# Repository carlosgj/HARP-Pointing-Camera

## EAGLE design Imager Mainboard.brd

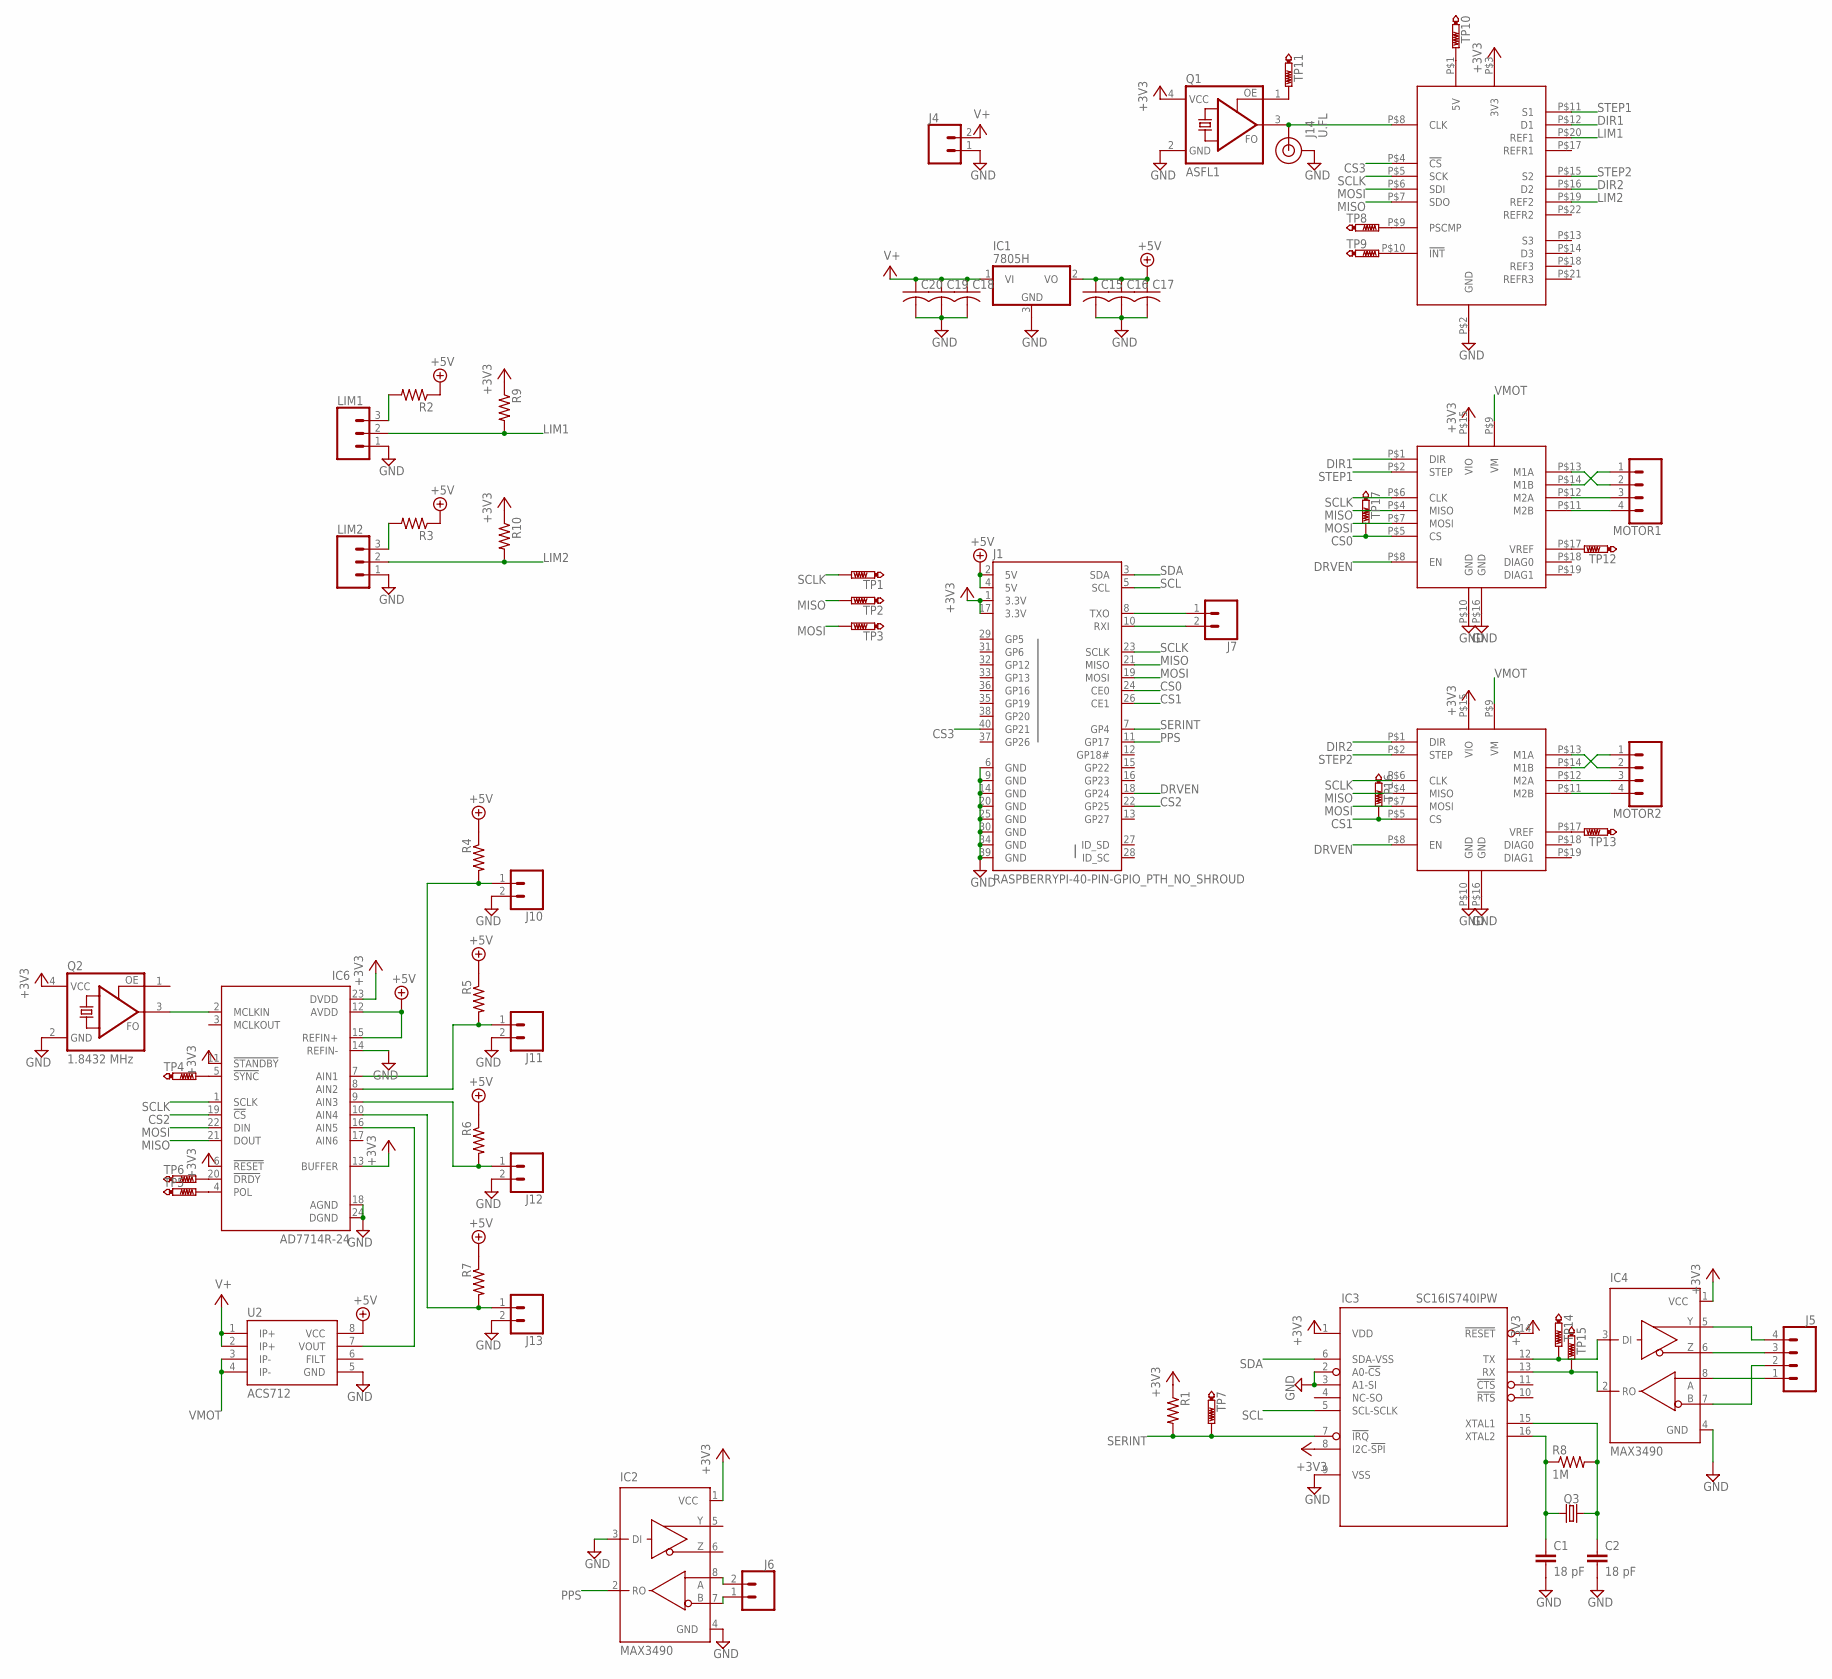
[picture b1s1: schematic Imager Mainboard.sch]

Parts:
C1, C2: 18 pF; C1206
C15, C16, C17, C18, C19, C20: C-USC1206; C1206
DRV1, DRV2: SILENTSTEPSTICK
IC1: 7805H; TO39
IC2, IC4: MAX3490; SO08
IC3: SC16IS740IPW; TSSOP16L
IC6: AD7714R-24; SO24R
J1: RASPBERRYPI-40-PIN-GPIO_PTH_NO_SHROUD; 2X20
J4, J6, J7, J10, J11, J12, J13: CONN_02; 1X02
J5: CONN_04; 1X04
J14: U.FL
LIM1, LIM2: CONN_03; 1X03
MOTOR1, MOTOR2: CONN_04; 1X04
Q1: ASFL1; ASF
Q2: 1.8432 MHz; ASF
Q3: CRYSTALSMD-5X3.2-4PAD; CRYSTAL-SMD-5X3.2-4PAD
R1, R2, R3, R4, R5, R6, R7, R9, R10: R-US_R1206; R1206
R8: 1M; R1206
TP1, TP2, TP3, TP8, TP9, TP10, TP11, TP12, TP13, TP14, TP15, TP16, TP17: PTR1PAD1-13; P1-13
TP4, TP5, TP6, TP7: PTR1B1,27; B1,27
U2: ACS712; SO08
U$1: TMC429-BOB

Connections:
+3V3: DRV1.P$15 (VIO), DRV2.P$15 (VIO), IC2.1 (VCC), IC3.1 (VDD), IC3.8 (I2C-!SPI), IC3.14 (!RESET), IC4.1 (VCC), IC6.6 (!RESET), IC6.11 (!STANDBY), IC6.13 (BUFFER), IC6.23 (DVDD), J1.1 (3.3V), J1.17 (3.3V), Q1.4 (VCC), Q2.4 (VCC), R1.1, R9.1, R10.1, U$1.P$3 (3V3)
+5V: C15.1, C16.1, C17.1, IC1.2 (VO), IC6.12 (AVDD), IC6.15 (REFIN+), J1.2 (5V), J1.4 (5V), R2.1, R3.1, R4.1, R5.1, R6.1, R7.1, U2.8 (VCC)
CS0: DRV1.P$5 (CS), J1.24 (CE0), TP17.TP
CS1: DRV2.P$5 (CS), J1.26 (CE1), TP16.TP
CS2: IC6.19 (!CS), J1.22 (GP25)
CS3: J1.40 (GP21), U$1.P$4 (!CS)
DIR1: DRV1.P$1 (DIR), U$1.P$12 (D1)
DIR2: DRV2.P$1 (DIR), U$1.P$16 (D2)
DRVEN: DRV1.P$8 (EN), DRV2.P$8 (EN), J1.18 (GP24)
GND: C1.2, C2.2, C15.2, C16.2, C17.2, C18.2, C19.2, C20.2, DRV1.P$10 (GND), DRV1.P$16 (GND), DRV2.P$10 (GND), DRV2.P$16 (GND), IC1.3 (GND), IC2.3 (DI), IC2.4 (GND), IC3.2 (A0-!CS), IC3.3 (A1-SI), IC3.9 (VSS), IC4.4 (GND), IC6.14 (REFIN-), IC6.18 (AGND), IC6.24 (DGND), J1.6 (GND), J1.9 (GND), J1.14 (GND), J1.20 (GND), J1.25 (GND), J1.30 (GND), J1.34 (GND), J1.39 (GND), J4.1, J10.2, J11.2, J12.2, J13.2, J14.1 (GND), J14.2 (GND), LIM1.1, LIM2.1, Q1.2 (GND), Q2.2 (GND), U2.5 (GND), U$1.P$2 (GND)
LIM1: LIM1.2, R9.2, U$1.P$20 (REF1)
LIM2: LIM2.2, R10.2, U$1.P$19 (REF2)
MISO: DRV1.P$4 (MISO), DRV2.P$4 (MISO), IC6.21 (DOUT), J1.21 (MISO), TP2.TP, U$1.P$7 (SDO)
MOSI: DRV1.P$7 (MOSI), DRV2.P$7 (MOSI), IC6.22 (DIN), J1.19 (MOSI), TP3.TP, U$1.P$6 (SDI)
unnamed: DRV2.P$14 (M1B), MOTOR2.1
unnamed: DRV2.P$13 (M1A), MOTOR2.2
unnamed: IC3.12 (TX), IC4.3 (DI), TP14.TP
unnamed: DRV2.P$12 (M2A), MOTOR2.3
unnamed: DRV2.P$11 (M2B), MOTOR2.4
unnamed: DRV1.P$14 (M1B), MOTOR1.1
unnamed: DRV1.P$13 (M1A), MOTOR1.2
unnamed: DRV1.P$12 (M2A), MOTOR1.3
unnamed: DRV1.P$11 (M2B), MOTOR1.4
unnamed: J1.8 (TXO), J7.1
unnamed: J1.10 (RXI), J7.2
unnamed: IC6.2 (MCLKIN), Q2.3 (FO)
unnamed: IC6.5 (!SYNC), TP4.TP
unnamed: LIM1.3, R2.2
unnamed: J14.FEED (SIGNAL), Q1.3 (FO), U$1.P$8 (CLK)
unnamed: LIM2.3, R3.2
unnamed: IC6.4 (POL), TP5.TP
unnamed: IC6.16 (AIN5), U2.7 (VOUT)
unnamed: IC6.20 (!DRDY), TP6.TP
unnamed: IC6.7 (AIN1), J10.1, R4.2
unnamed: TP8.TP, U$1.P$9 (PSCMP)
unnamed: IC6.8 (AIN2), J11.1, R5.2
unnamed: IC6.9 (AIN3), J12.1, R6.2
unnamed: IC6.10 (AIN4), J13.1, R7.2
unnamed: TP9.TP, U$1.P$10 (!INT)
unnamed: TP10.TP, U$1.P$1 (5V)
unnamed: Q1.1 (OE), TP11.TP
unnamed: DRV1.P$17 (VREF), TP12.TP
unnamed: DRV2.P$17 (VREF), TP13.TP
unnamed: C2.1, IC3.15 (XTAL1), Q3.3 (2), R8.2
unnamed: C1.1, IC3.16 (XTAL2), Q3.1, R8.1
unnamed: IC3.13 (RX), IC4.2 (RO), TP15.TP
unnamed: IC4.6 (Z), J5.3
unnamed: IC4.8 (A), J5.1
unnamed: IC4.7 (B), J5.2
unnamed: IC4.5 (Y), J5.4
unnamed: IC2.7 (B), J6.1
unnamed: IC2.8 (A), J6.2
PPS: IC2.2 (RO), J1.11 (GP17)
SCL: IC3.5 (SCL-SCLK), J1.5 (SCL)
SCLK: DRV1.P$6 (CLK), DRV2.P$6 (CLK), IC6.1 (SCLK), J1.23 (SCLK), TP1.TP, U$1.P$5 (SCK)
SDA: IC3.6 (SDA-VSS), J1.3 (SDA)
SERINT: IC3.7 (!IRQ), J1.7 (GP4), R1.2, TP7.TP
STEP1: DRV1.P$2 (STEP), U$1.P$11 (S1)
STEP2: DRV2.P$2 (STEP), U$1.P$15 (S2)
V+: C18.1, C19.1, C20.1, IC1.1 (VI), J4.2, U2.1 (IP+), U2.2 (IP+)
VMOT: DRV1.P$9 (VM), DRV2.P$9 (VM), U2.3 (IP-), U2.4 (IP-)

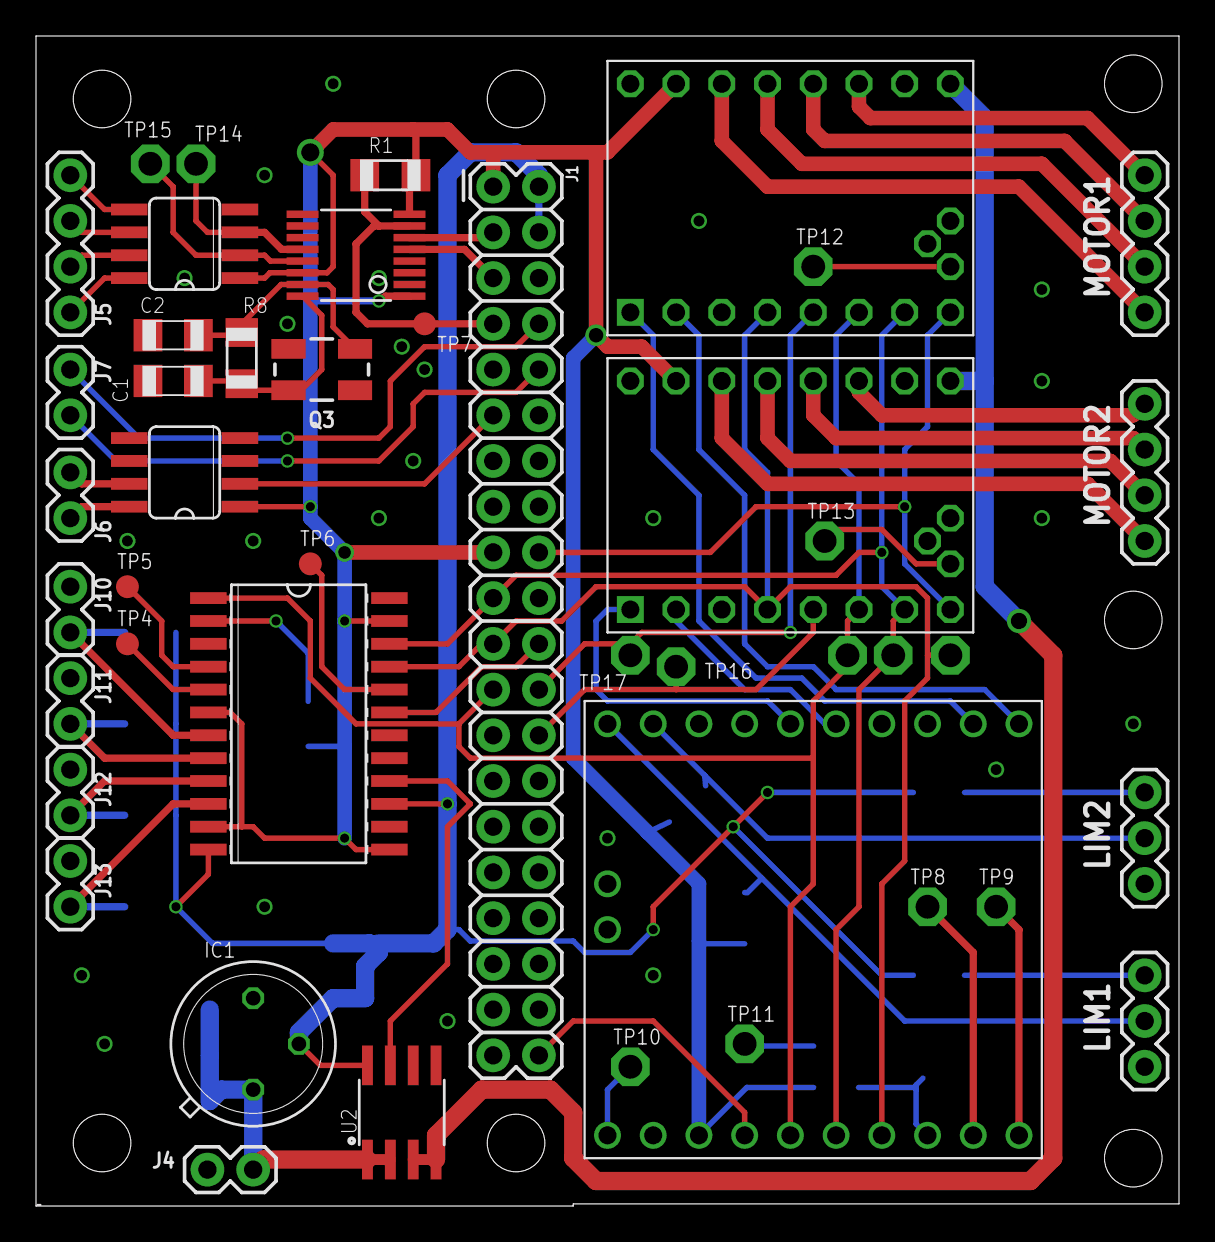
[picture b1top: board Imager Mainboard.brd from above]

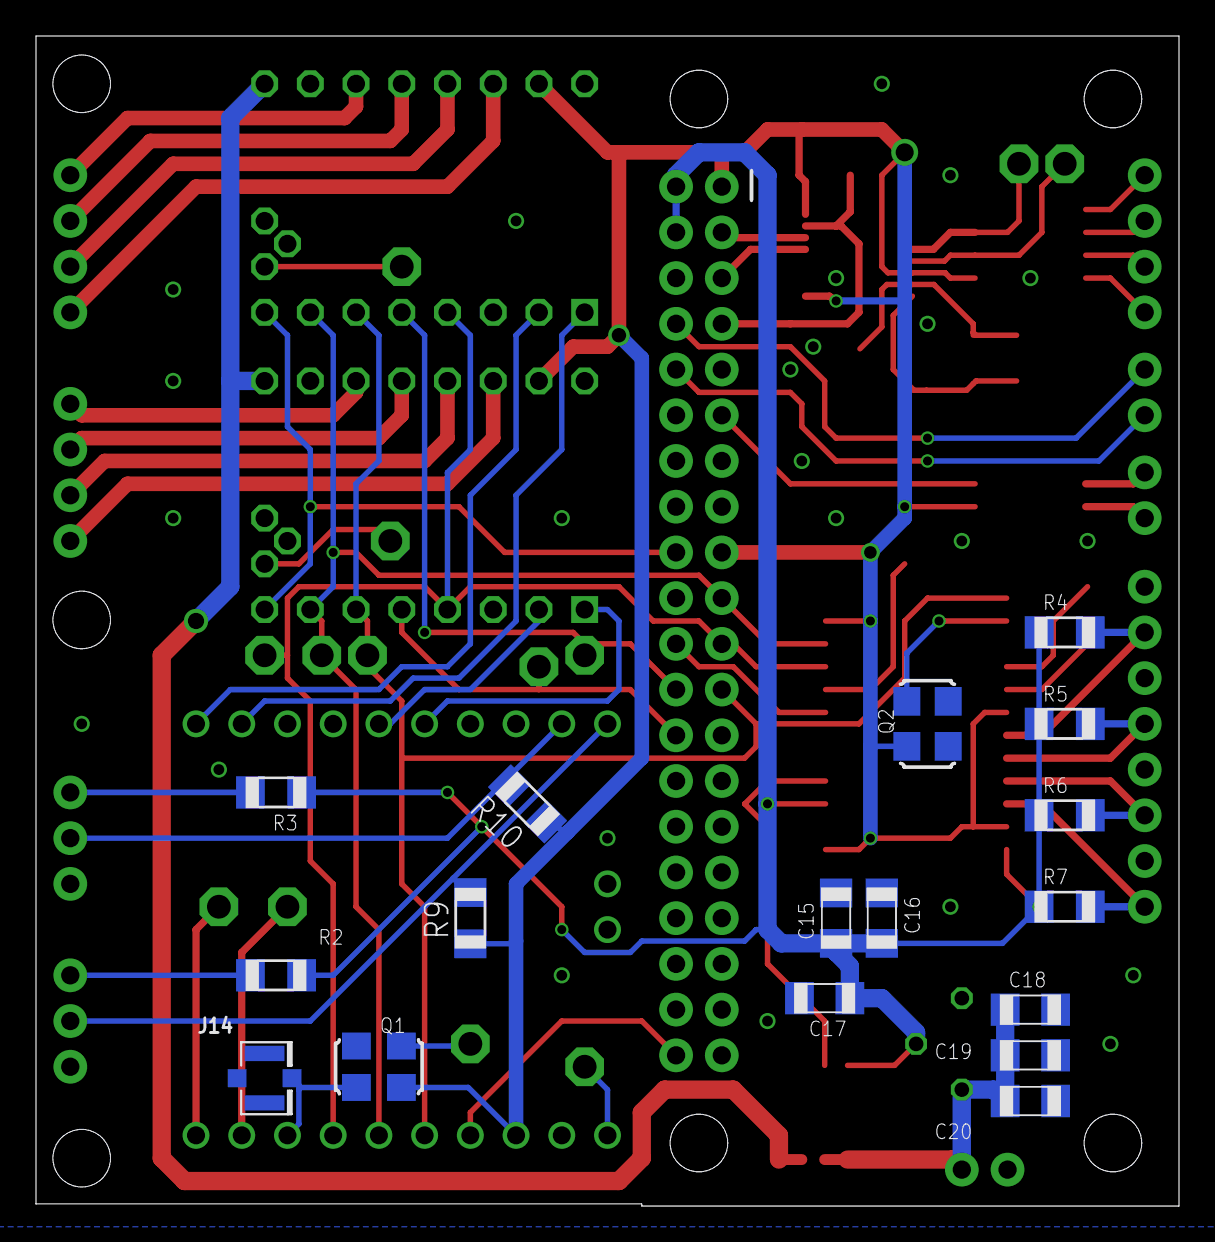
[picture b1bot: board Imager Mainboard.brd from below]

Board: 2 copper layers, 63.5 x 65.0 mm, 61 parts (17 on the bottom side), 61 nets.

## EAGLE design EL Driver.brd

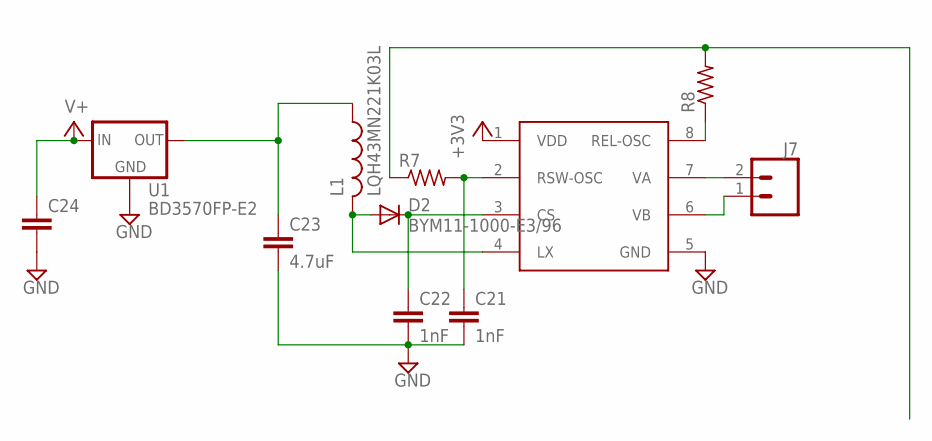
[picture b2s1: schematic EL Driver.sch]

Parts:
C21, C22: 1nF; C1206
C23: 4.7uF; C1206
C24: C-EUC1206; C1206
D2: BYM11-1000-E3/96; MELF-MLL41
J7: CONN_02; 1X02
L1: LQH43MN221K03L; L1812
R7, R8: R-US_R1206; R1206
U1: BD3570FP-E2; TO-252
U$3: HV830; SOIC8

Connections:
+3V3: U$3.1 (VDD)
GND: C21.2, C22.2, C23.2, C24.2, U1.3 (GND), U$3.5 (GND)
unnamed: J7.2, U$3.7 (VA)
unnamed: J7.1, U$3.6 (VB)
unnamed: C22.1, D2.C, U$3.3 (CS)
unnamed: D2.A, L1.2, U$3.4 (LX)
unnamed: C21.1, R7.2, U$3.2 (RSW-OSC)
unnamed: R8.1, U$3.8 (REL-OSC)
unnamed: R7.1, R8.2
unnamed: C23.1, L1.1, U1.2 (OUT)
V+: C24.1, U1.1 (IN)

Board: 2 copper layers, 11 parts (6 on the bottom side), 10 nets, no tracks yet.

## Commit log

2020-07-26 Stepper driver test code
2020-07-26 The TMC429 is basically working with a TMC2130
2020-07-27 TMC429 works with both motors
2020-07-27 Moving CAD in from Telescope-Design
2020-07-27 High-level code work
2020-07-27 Electronics design
2020-07-27 Documentation
2020-07-28 Adding code reset
2020-07-29 Working on comm code
2020-07-30 Working on integrating flight software
2020-08-02 Adding homing routine
2020-08-05 Working on TMC2130 manager
2020-08-08 Working on single-threaded code
2020-08-11 Adding test pads
2020-08-14 Adding shadow registers
2020-08-18 CTDB updates
2020-08-18 Adding register defs
2020-08-19 Adding homing code
2020-08-21 Working on shared object passing
2020-08-22 Adding stuff for shared object
2020-08-22 Working on implementing threaded architecture
2020-08-22 Logging and debugging
2020-08-23 Adding shutdown command
2020-08-24 Bugfix
2020-08-24 Adding opcodes
2020-08-24 Homing behavior updates
2020-08-24 Adding TMC429 CS
2020-08-24 Adding correct SPI CS addresses
2020-08-24 Correcting SPI CS
2020-08-24 Adding serial test points
2020-08-27 Removing SPI mockup code
2020-08-28 Adding mock
2020-08-28 Working on helper functions and documentation
2020-08-28 Implementing opcodes
2020-08-28 Removing DFC, FFC (easier to just command the angles & a collect)
2020-08-28 Working on raw Bayer processing
2020-08-28 Moving serial config up to FSW
2020-08-28 Implementing camera code
2020-08-29 Debayering seems to work properly now
2020-08-29 This algorithm preserves resolution
2020-08-29 Homing & boresight routines work
2020-08-29 Adding SC16IS740 oscillator section and limit switch pullups
2020-09-10 Camera integration work
2020-09-10 Adding COSMOS
2020-09-10 COSMOS work
2020-09-18 Pipeline mostly works
2020-09-22 Byte stuffing
2021-02-09 Bump nokogiri from 1.10.10 to 1.11.1 in /COSMOS/HAB/config/dart
    Bumps [nokogiri](https://github.com/sparklemotion/nokogiri) from 1.10.10 to 1.11.1.
    - [Release notes](https://github.com/sparklemotion/nokogiri/releases)
    - [Changelog](https://github.com/sparklemotion/nokogiri/blob/main/CHANGELOG.md)
    - [Commits](https://github.com/sparklemotion/nokogiri/compare/v1.10.10...v1.11.1)
2021-05-20 Bump puma from 3.12.6 to 4.3.8 in /COSMOS/HAB/config/dart
    Bumps [puma](https://github.com/puma/puma) from 3.12.6 to 4.3.8.
    - [Release notes](https://github.com/puma/puma/releases)
    - [Changelog](https://github.com/puma/puma/blob/master/History.md)
    - [Commits](https://github.com/puma/puma/compare/v3.12.6...v4.3.8)
2021-05-20 Bump nokogiri from 1.10.10 to 1.11.5 in /COSMOS/HAB/config/dart
    Bumps [nokogiri](https://github.com/sparklemotion/nokogiri) from 1.10.10 to 1.11.5.
    - [Release notes](https://github.com/sparklemotion/nokogiri/releases)
    - [Changelog](https://github.com/sparklemotion/nokogiri/blob/main/CHANGELOG.md)
    - [Commits](https://github.com/sparklemotion/nokogiri/compare/v1.10.10...v1.11.5)
2021-09-28 Bump nokogiri from 1.10.10 to 1.12.5 in /COSMOS/HAB/config/dart
    Bumps [nokogiri](https://github.com/sparklemotion/nokogiri) from 1.10.10 to 1.12.5.
    - [Release notes](https://github.com/sparklemotion/nokogiri/releases)
    - [Changelog](https://github.com/sparklemotion/nokogiri/blob/main/CHANGELOG.md)
    - [Commits](https://github.com/sparklemotion/nokogiri/compare/v1.10.10...v1.12.5)
    ---
    updated-dependencies:
2021-10-12 Bump puma from 3.12.6 to 4.3.9 in /COSMOS/HAB/config/dart
    Bumps [puma](https://github.com/puma/puma) from 3.12.6 to 4.3.9.
    - [Release notes](https://github.com/puma/puma/releases)
    - [Changelog](https://github.com/puma/puma/blob/master/History.md)
    - [Commits](https://github.com/puma/puma/compare/v3.12.6...v4.3.9)
    ---
    updated-dependencies:
2022-02-12 Bump puma from 3.12.6 to 4.3.11 in /COSMOS/HAB/config/dart
    Bumps [puma](https://github.com/puma/puma) from 3.12.6 to 4.3.11.
    - [Release notes](https://github.com/puma/puma/releases)
    - [Changelog](https://github.com/puma/puma/blob/master/History.md)
    - [Commits](https://github.com/puma/puma/compare/v3.12.6...v4.3.11)
    ---
    updated-dependencies:
2022-02-26 Bump nokogiri from 1.10.10 to 1.13.3 in /COSMOS/HAB/config/dart
    Bumps [nokogiri](https://github.com/sparklemotion/nokogiri) from 1.10.10 to 1.13.3.
    - [Release notes](https://github.com/sparklemotion/nokogiri/releases)
    - [Changelog](https://github.com/sparklemotion/nokogiri/blob/main/CHANGELOG.md)
    - [Commits](https://github.com/sparklemotion/nokogiri/compare/v1.10.10...v1.13.3)
    ---
    updated-dependencies:
2022-03-31 Bump puma from 3.12.6 to 4.3.12 in /COSMOS/HAB/config/dart
    Bumps [puma](https://github.com/puma/puma) from 3.12.6 to 4.3.12.
    - [Release notes](https://github.com/puma/puma/releases)
    - [Changelog](https://github.com/puma/puma/blob/master/History.md)
    - [Commits](https://github.com/puma/puma/compare/v3.12.6...v4.3.12)
    ---
    updated-dependencies:
2022-04-12 Bump nokogiri from 1.10.10 to 1.13.4 in /COSMOS/HAB/config/dart
    Bumps [nokogiri](https://github.com/sparklemotion/nokogiri) from 1.10.10 to 1.13.4.
    - [Release notes](https://github.com/sparklemotion/nokogiri/releases)
    - [Changelog](https://github.com/sparklemotion/nokogiri/blob/v1.13.4/CHANGELOG.md)
    - [Commits](https://github.com/sparklemotion/nokogiri/compare/v1.10.10...v1.13.4)
    ---
    updated-dependencies:
2022-05-19 Bump nokogiri from 1.10.10 to 1.13.6 in /COSMOS/HAB/config/dart
    Bumps [nokogiri](https://github.com/sparklemotion/nokogiri) from 1.10.10 to 1.13.6.
    - [Release notes](https://github.com/sparklemotion/nokogiri/releases)
    - [Changelog](https://github.com/sparklemotion/nokogiri/blob/main/CHANGELOG.md)
    - [Commits](https://github.com/sparklemotion/nokogiri/compare/v1.10.10...v1.13.6)
    ---
    updated-dependencies:
2022-07-06 Bump rails-html-sanitizer from 1.3.0 to 1.4.3 in /COSMOS/HAB/config/dart
    Bumps [rails-html-sanitizer](https://github.com/rails/rails-html-sanitizer) from 1.3.0 to 1.4.3.
    - [Release notes](https://github.com/rails/rails-html-sanitizer/releases)
    - [Changelog](https://github.com/rails/rails-html-sanitizer/blob/master/CHANGELOG.md)
    - [Commits](https://github.com/rails/rails-html-sanitizer/compare/v1.3.0...v1.4.3)
    ---
    updated-dependencies:
2022-07-22 Bump tzinfo from 1.2.7 to 1.2.10 in /COSMOS/HAB/config/dart
    Bumps [tzinfo](https://github.com/tzinfo/tzinfo) from 1.2.7 to 1.2.10.
    - [Release notes](https://github.com/tzinfo/tzinfo/releases)
    - [Changelog](https://github.com/tzinfo/tzinfo/blob/master/CHANGES.md)
    - [Commits](https://github.com/tzinfo/tzinfo/compare/v1.2.7...v1.2.10)
    ---
    updated-dependencies:
2022-12-14 Bump loofah from 2.7.0 to 2.19.1 in /COSMOS/HAB/config/dart
    Bumps [loofah](https://github.com/flavorjones/loofah) from 2.7.0 to 2.19.1.
    - [Release notes](https://github.com/flavorjones/loofah/releases)
    - [Changelog](https://github.com/flavorjones/loofah/blob/main/CHANGELOG.md)
    - [Commits](https://github.com/flavorjones/loofah/compare/v2.7.0...v2.19.1)
    ---
    updated-dependencies:
2022-12-14 Bump rails-html-sanitizer from 1.3.0 to 1.4.4 in /COSMOS/HAB/config/dart
    Bumps [rails-html-sanitizer](https://github.com/rails/rails-html-sanitizer) from 1.3.0 to 1.4.4.
    - [Release notes](https://github.com/rails/rails-html-sanitizer/releases)
    - [Changelog](https://github.com/rails/rails-html-sanitizer/blob/master/CHANGELOG.md)
    - [Commits](https://github.com/rails/rails-html-sanitizer/compare/v1.3.0...v1.4.4)
    ---
    updated-dependencies:
2023-01-18 Bump rack from 2.2.3 to 2.2.6.2 in /COSMOS/HAB/config/dart
    Bumps [rack](https://github.com/rack/rack) from 2.2.3 to 2.2.6.2.
    - [Release notes](https://github.com/rack/rack/releases)
    - [Changelog](https://github.com/rack/rack/blob/main/CHANGELOG.md)
    - [Commits](https://github.com/rack/rack/compare/2.2.3...v2.2.6.2)
    ---
    updated-dependencies:
2023-01-19 Bump globalid from 0.4.2 to 1.0.1 in /COSMOS/HAB/config/dart
    Bumps [globalid](https://github.com/rails/globalid) from 0.4.2 to 1.0.1.
    - [Release notes](https://github.com/rails/globalid/releases)
    - [Commits](https://github.com/rails/globalid/compare/v0.4.2...v1.0.1)
    ---
    updated-dependencies:
    - dependency-name: globalid
2023-03-08 Bump rack from 2.2.3 to 2.2.6.3 in /COSMOS/HAB/config/dart
    Bumps [rack](https://github.com/rack/rack) from 2.2.3 to 2.2.6.3.
    - [Release notes](https://github.com/rack/rack/releases)
    - [Changelog](https://github.com/rack/rack/blob/main/CHANGELOG.md)
    - [Commits](https://github.com/rack/rack/compare/2.2.3...v2.2.6.3)
    ---
    updated-dependencies:
2023-03-08 Bump nokogiri from 1.10.10 to 1.14.2 in /COSMOS/HAB/config/dart
    Bumps [nokogiri](https://github.com/sparklemotion/nokogiri) from 1.10.10 to 1.14.2.
    - [Release notes](https://github.com/sparklemotion/nokogiri/releases)
    - [Changelog](https://github.com/sparklemotion/nokogiri/blob/main/CHANGELOG.md)
    - [Commits](https://github.com/sparklemotion/nokogiri/compare/v1.10.10...v1.14.2)
    ---
    updated-dependencies:

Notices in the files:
parts and their libraries:
SparkFun-Connectors: Licensing: Creative Commons ShareAlike 4.0 International - https://creativecommons.org/licenses/by-sa/4.0
